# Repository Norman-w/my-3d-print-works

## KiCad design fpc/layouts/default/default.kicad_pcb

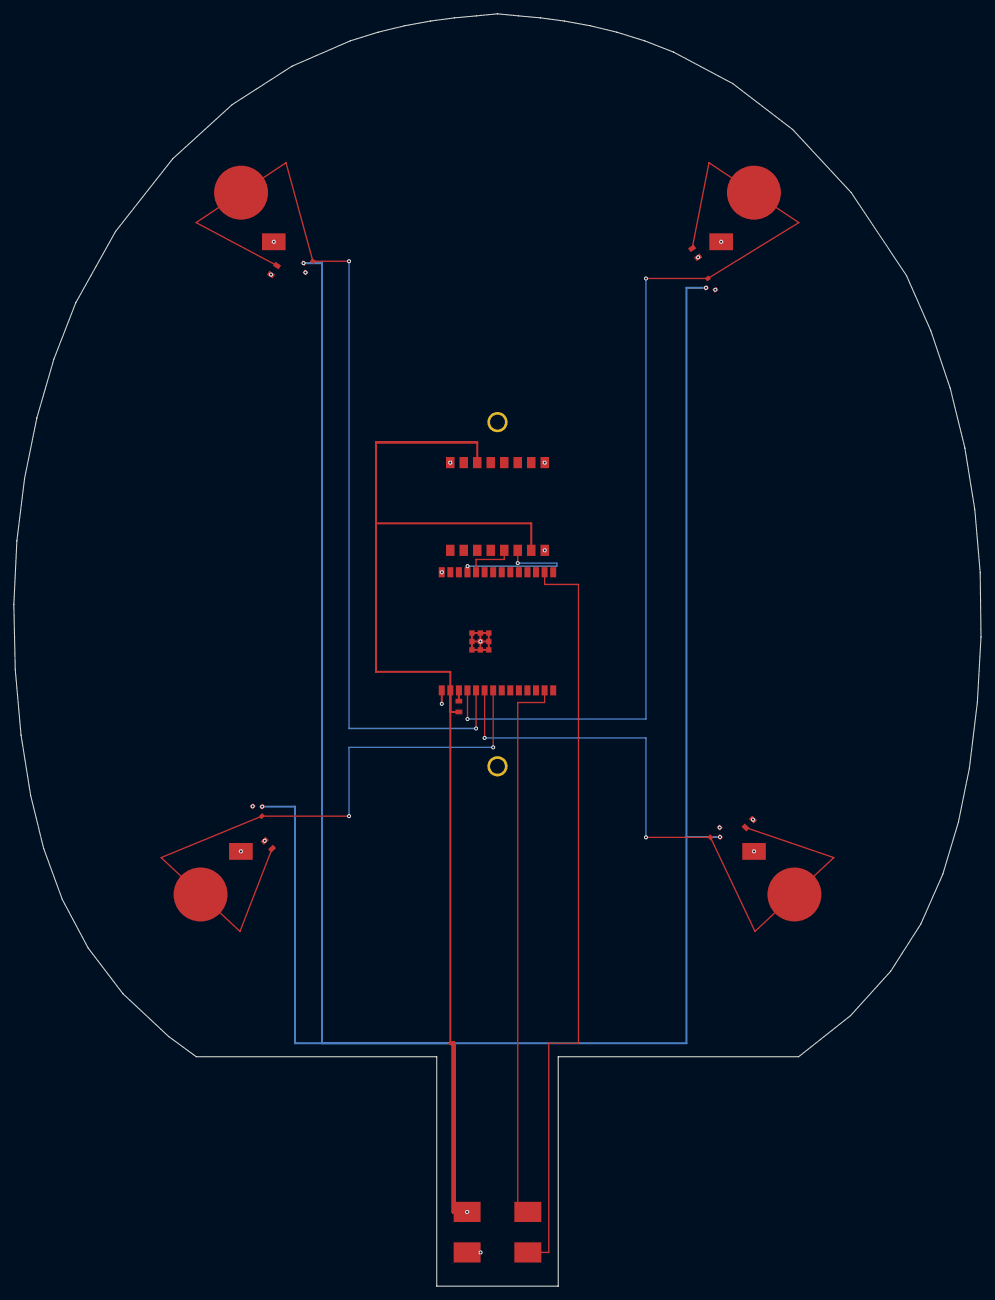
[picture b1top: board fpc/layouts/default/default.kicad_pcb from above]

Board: 2 copper layers, 143.3 x 188.5 mm, 19 parts (0 on the bottom side), 11 nets.

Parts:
D_PZT_BL: BAT54S
D_PZT_BR: BAT54S
D_PZT_TL: BAT54S
D_PZT_TR: BAT54S
J1: ESP32-C6-WROOM-1
PZT_BL: PZT-5A
PZT_BR: PZT-5A
PZT_TL: PZT-5A
PZT_TR: PZT-5A
R_EN: 10k
R_PZT_BL: 1M
R_PZT_BR: 1M
R_PZT_TL: 1M
R_PZT_TR: 1M
TP_D+: D+
TP_D-: D-
TP_GND: GND
TP_VCC: VCC
U1: IM948

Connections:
EN: J1.3, R_EN.1
GND: D_PZT_BL.2, D_PZT_BR.2, D_PZT_TL.2, D_PZT_TR.2, J1.1, J1.28, J1.29, PZT_BL.2, PZT_BR.2, PZT_TL.2, PZT_TR.2, R_PZT_BL.2, R_PZT_BR.2, R_PZT_TL.2, R_PZT_TR.2, TP_GND.1, U1.1, U1.8, U1.16
PZT_BL_SIGNAL: D_PZT_BL.1, J1.7, PZT_BL.1, R_PZT_BL.1
PZT_BR_SIGNAL: D_PZT_BR.1, J1.6, PZT_BR.1, R_PZT_BR.1
PZT_TL_SIGNAL: D_PZT_TL.1, J1.5, PZT_TL.1, R_PZT_TL.1
PZT_TR_SIGNAL: D_PZT_TR.1, J1.4, PZT_TR.1, R_PZT_TR.1
UART_RX: J1.25, U1.14
UART_TX: J1.24, U1.13
USB_D+: J1.13, TP_D+.1
USB_D-: J1.16, TP_D-.1
VCC: D_PZT_BL.3, D_PZT_BR.3, D_PZT_TL.3, D_PZT_TR.3, J1.2, R_EN.2, TP_VCC.1, U1.3, U1.15

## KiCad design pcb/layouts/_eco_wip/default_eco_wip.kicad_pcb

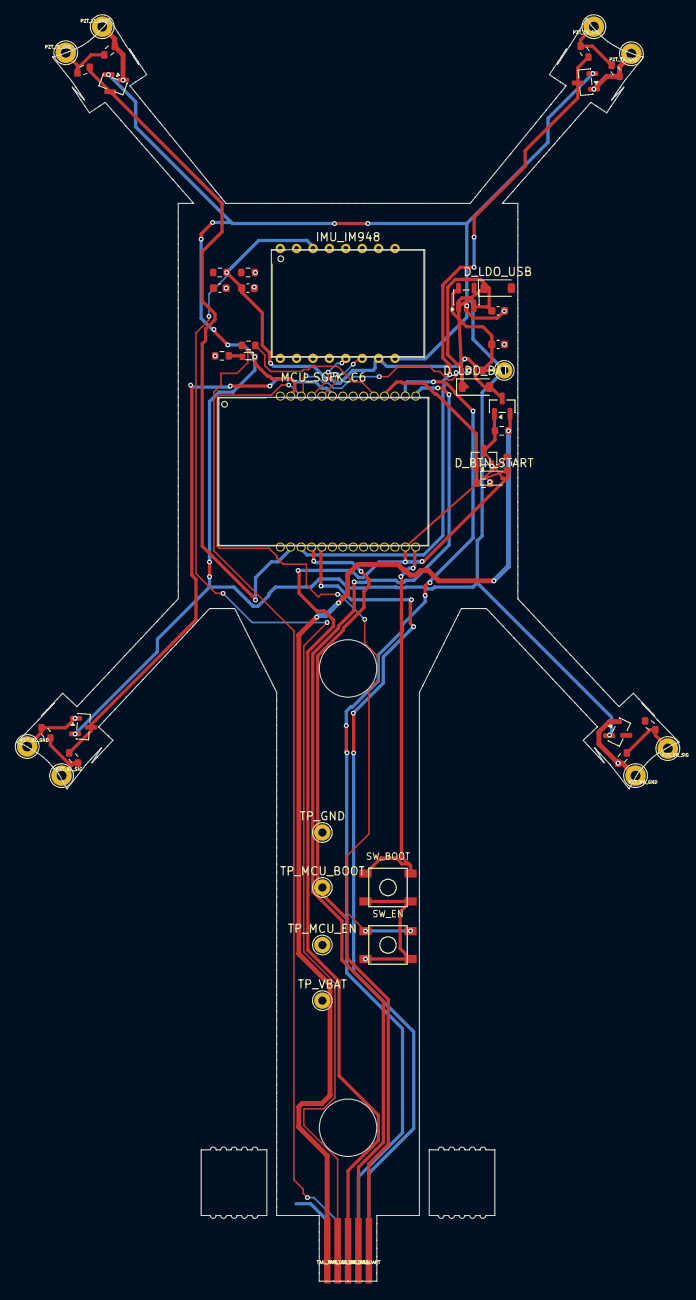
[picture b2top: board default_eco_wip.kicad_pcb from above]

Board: 2 copper layers, 80.8 x 153.9 mm, 53 parts (0 on the bottom side), 30 nets.

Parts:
BAT_C_ADC_100N: C_0603_1608Metric
BAT_R_BOT_1M: R_0603_1608Metric
BAT_R_TOP_1M: R_0603_1608Metric
D_BTN_START: 1N4148W; D_SOD-323
D_LDO_BAT: SS14; D_SOD-123
D_LDO_USB: SS14; D_SOD-123
IMU_IM948: IM948_CUTOUT
LED_C_SUP_100N: C_0603_1608Metric
LED_MCU_PWR: LED_0603
LED_R_DATA_330R: R_0603_1608Metric
MCU_SGFK_C6: SGFK_ESP32-C6-N8_CUTOUT
PW_C_IN_10U: C_0603_1608Metric
PW_C_OUT_10U: C_0603_1608Metric
PW_LDO_3V3: SOT-23-5
PW_Q_LATCH: SOT-23
PW_Q_LOAD: SOT-23
PW_R_BTN_SER_1K: 1k; R_0603_1608Metric
PW_R_EN_PU_10K: R_0603_1608Metric
PW_R_GATE_100K: R_0603_1608Metric
PW_R_LATCH_PD_100K: R_0603_1608Metric
PZT_BL_D_CLAMP: SOT-23
PZT_BL_GND: TestPoint_THTPad_D2.5mm_Drill1.2mm
PZT_BL_R_DIS_1M: R_0603_1608Metric
PZT_BL_R_SER_4K7: R_0603_1608Metric
PZT_BL_SIG: TestPoint_THTPad_D2.5mm_Drill1.2mm
PZT_BR_D_CLAMP: SOT-23
PZT_BR_GND: TestPoint_THTPad_D2.5mm_Drill1.2mm
PZT_BR_R_DIS_1M: R_0603_1608Metric
PZT_BR_R_SER_4K7: R_0603_1608Metric
PZT_BR_SIG: TestPoint_THTPad_D2.5mm_Drill1.2mm
PZT_TL_D_CLAMP: SOT-23
PZT_TL_GND: TestPoint_THTPad_D2.5mm_Drill1.2mm
PZT_TL_R_DIS_1M: R_0603_1608Metric
PZT_TL_R_SER_4K7: R_0603_1608Metric
PZT_TL_SIG: TestPoint_THTPad_D2.5mm_Drill1.2mm
PZT_TR_D_CLAMP: SOT-23
PZT_TR_GND: TestPoint_THTPad_D2.5mm_Drill1.2mm
PZT_TR_R_DIS_1M: R_0603_1608Metric
PZT_TR_R_SER_4K7: R_0603_1608Metric
PZT_TR_SIG: TestPoint_THTPad_D2.5mm_Drill1.2mm
R_MCU_PWR_1K: R_0603_1608Metric
SW_BOOT: 4.5x4.5; SW_SPST_4.5x4.5
SW_EN: 4.5x4.5; SW_SPST_4.5x4.5
TAIL_CTL: EdgeFingerPad_P1.27mm_Dual
TAIL_LED: EdgeFingerPad_P1.27mm_Dual
TAIL_PWR: EdgeFingerPad_P1.27mm_Dual
TAIL_UART: EdgeFingerPad_P1.27mm_Dual
TAIL_USB: EdgeFingerPad_P1.27mm_Dual
TP_3V3: 3V3; TestPoint_THTPad_D2.0mm_Drill1.0mm
TP_GND: GND; TestPoint_THTPad_D2.0mm_Drill1.0mm
TP_MCU_BOOT: BOOT; TestPoint_THTPad_D2.0mm_Drill1.0mm
TP_MCU_EN: EN; TestPoint_THTPad_D2.0mm_Drill1.0mm
TP_VBAT: VBAT_SW; TestPoint_THTPad_D2.0mm_Drill1.0mm

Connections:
BOOT: MCU_SGFK_C6.15, SW_BOOT.1, TP_MCU_BOOT.1
EN: MCU_SGFK_C6.3, PW_R_EN_PU_10K.1, SW_EN.1, TP_MCU_EN.1
PWR_LATCH: MCU_SGFK_C6.11, PW_Q_LATCH.1, PW_R_LATCH_PD_100K.1
UART_RX: MCU_SGFK_C6.24, TAIL_UART.B
UART_TX: MCU_SGFK_C6.25, TAIL_UART.F
USB_DN: MCU_SGFK_C6.13, TAIL_USB.B
USB_DP: MCU_SGFK_C6.14, TAIL_USB.F
USB_VBUS: D_LDO_USB.2, IMU_IM948.2, TAIL_CTL.B
VBAT_SW: BAT_R_TOP_1M.1, D_LDO_BAT.2, IMU_IM948.3, IMU_IM948.15, LED_C_SUP_100N.1, PW_Q_LOAD.3, TAIL_LED.F, TP_VBAT.1
bleed_resistor-SIGNAL_PAD-0: PZT_BL_R_DIS_1M.1, PZT_BL_R_SER_4K7.1, PZT_BL_SIG.1
bleed_resistor-SIGNAL_PAD-1: PZT_BR_R_DIS_1M.1, PZT_BR_R_SER_4K7.1, PZT_BR_SIG.1
bleed_resistor-SIGNAL_PAD-2: PZT_TL_R_DIS_1M.1, PZT_TL_R_SER_4K7.1, PZT_TL_SIG.1
bleed_resistor-SIGNAL_PAD-3: PZT_TR_R_DIS_1M.1, PZT_TR_R_SER_4K7.1, PZT_TR_SIG.1
btn_sw: D_BTN_START.1, PW_R_BTN_SER_1K.1, TAIL_CTL.F
c: LED_MCU_PWR.2, R_MCU_PWR_1K.1
gnd: BAT_C_ADC_100N.2, BAT_R_BOT_1M.2, IMU_IM948.1, IMU_IM948.8, IMU_IM948.16, LED_C_SUP_100N.2, MCU_SGFK_C6.1, MCU_SGFK_C6.28, PW_C_IN_10U.2, PW_C_OUT_10U.2, PW_LDO_3V3.2, PW_Q_LATCH.2, PW_R_LATCH_PD_100K.2, PZT_BL_D_CLAMP.1, PZT_BL_GND.1, PZT_BL_R_DIS_1M.2, PZT_BR_D_CLAMP.1, PZT_BR_GND.1, PZT_BR_R_DIS_1M.2, PZT_TL_D_CLAMP.1, PZT_TL_GND.1, PZT_TL_R_DIS_1M.2, PZT_TR_D_CLAMP.1, PZT_TR_GND.1, PZT_TR_R_DIS_1M.2, R_MCU_PWR_1K.2, SW_BOOT.2, SW_EN.2, TAIL_PWR.B, TP_GND.1
imu_uart_rx: IMU_IM948.14, MCU_SGFK_C6.5
imu_uart_tx: IMU_IM948.13, MCU_SGFK_C6.4
ldo_vin: D_LDO_BAT.1, D_LDO_USB.1, PW_C_IN_10U.1, PW_LDO_3V3.1, PW_LDO_3V3.3
led_data: LED_R_DATA_330R.1, MCU_SGFK_C6.10
led_din: LED_R_DATA_330R.2, TAIL_LED.B
p_gate: D_BTN_START.2, PW_Q_LATCH.3, PW_Q_LOAD.1, PW_R_GATE_100K.1
pzt_bl_signal: MCU_SGFK_C6.6, PZT_BL_D_CLAMP.3, PZT_BL_R_SER_4K7.2
pzt_br_signal: MCU_SGFK_C6.7, PZT_BR_D_CLAMP.3, PZT_BR_R_SER_4K7.2
pzt_tl_signal: MCU_SGFK_C6.27, PZT_TL_D_CLAMP.3, PZT_TL_R_SER_4K7.2
pzt_tr_signal: MCU_SGFK_C6.26, PZT_TR_D_CLAMP.3, PZT_TR_R_SER_4K7.2
user_btn: MCU_SGFK_C6.16, PW_R_BTN_SER_1K.2
vbat_in: PW_Q_LOAD.2, PW_R_GATE_100K.2, TAIL_PWR.F
vbat_sense: BAT_C_ADC_100N.1, BAT_R_BOT_1M.1, BAT_R_TOP_1M.2, IMU_IM948.7
vcc: LED_MCU_PWR.1, MCU_SGFK_C6.2, PW_C_OUT_10U.1, PW_LDO_3V3.5, PW_R_EN_PU_10K.2, PZT_BL_D_CLAMP.2, PZT_BR_D_CLAMP.2, PZT_TL_D_CLAMP.2, PZT_TR_D_CLAMP.2, TP_3V3.1

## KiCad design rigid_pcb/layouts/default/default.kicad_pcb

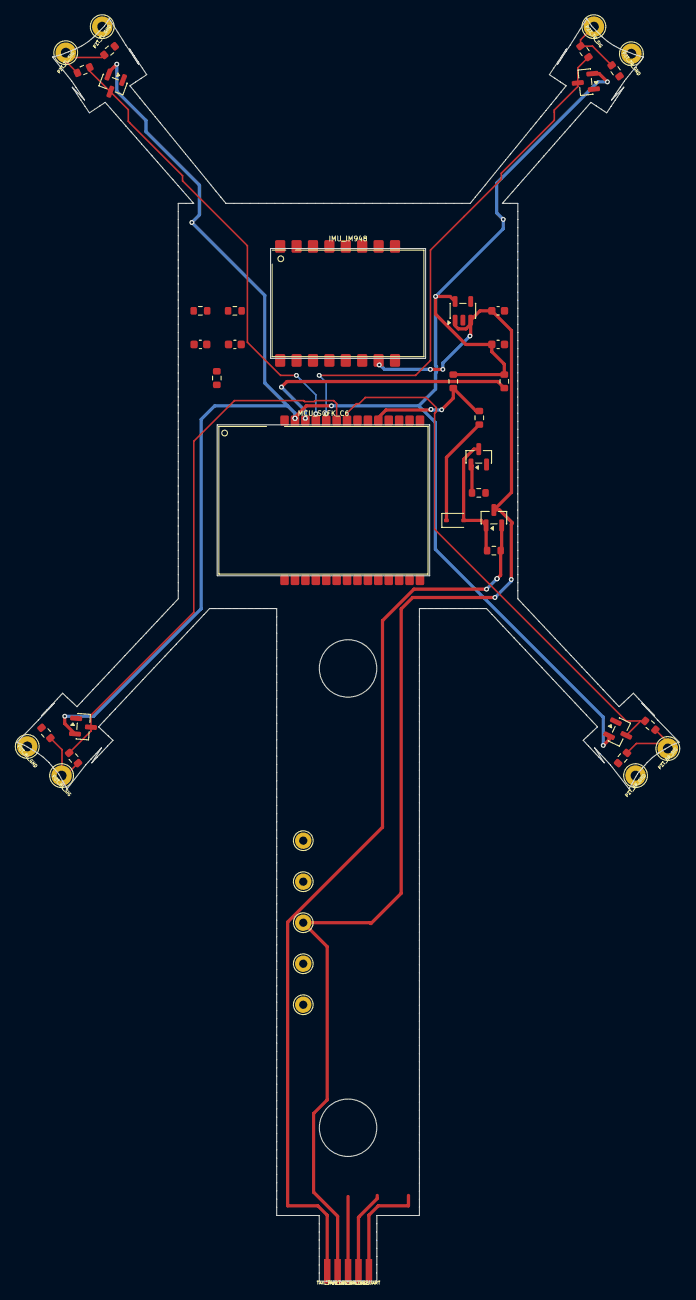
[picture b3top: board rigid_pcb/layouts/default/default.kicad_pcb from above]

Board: 2 copper layers, 80.8 x 153.9 mm, 48 parts (0 on the bottom side), 26 nets.

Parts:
BAT_C_ADC_100N: 100nF; C_0603_1608Metric
BAT_R_BOT_1M: 1M; R_0603_1608Metric
BAT_R_TOP_1M: 1M; R_0603_1608Metric
IMU_IM948: IM948; IM948_CUTOUT
LED_C_SUP_100N: 100nF; C_0603_1608Metric
LED_R_DATA_330R: 330R; R_0603_1608Metric
MCU_SGFK_C6: SGFK ESP32-C6-N8; SGFK_ESP32-C6-N8_CUTOUT
PW_C_IN_10U: 10uF; C_0603_1608Metric
PW_C_OUT_10U: 10uF; C_0603_1608Metric
PW_D_BTN: Schottky; D_SOD-323
PW_LDO_3V3: AP2112K-3.3; SOT-23-5
PW_Q_LATCH: N-MOS latch; SOT-23
PW_Q_LOAD: P-MOS load switch; SOT-23
PW_R_BTN_PU_10K: 10k; R_0603_1608Metric
PW_R_BTN_SER_1K: 1k; R_0603_1608Metric
PW_R_EN_PU_10K: 10k; R_0603_1608Metric
PW_R_GATE_100K: 100k; R_0603_1608Metric
PW_R_LATCH_PD_100K: 100k; R_0603_1608Metric
PZT_BL_D_CLAMP: BAT54S; SOT-23
PZT_BL_GND: PZT GND wire; TestPoint_THTPad_D2.5mm_Drill1.2mm
PZT_BL_R_DIS_1M: 1M; R_0603_1608Metric
PZT_BL_R_SER_4K7: 4.7k; R_0603_1608Metric
PZT_BL_SIG: PZT signal wire; TestPoint_THTPad_D2.5mm_Drill1.2mm
PZT_BR_D_CLAMP: BAT54S; SOT-23
PZT_BR_GND: PZT GND wire; TestPoint_THTPad_D2.5mm_Drill1.2mm
PZT_BR_R_DIS_1M: 1M; R_0603_1608Metric
PZT_BR_R_SER_4K7: 4.7k; R_0603_1608Metric
PZT_BR_SIG: PZT signal wire; TestPoint_THTPad_D2.5mm_Drill1.2mm
PZT_TL_D_CLAMP: BAT54S; SOT-23
PZT_TL_GND: PZT GND wire; TestPoint_THTPad_D2.5mm_Drill1.2mm
PZT_TL_R_DIS_1M: 1M; R_0603_1608Metric
PZT_TL_R_SER_4K7: 4.7k; R_0603_1608Metric
PZT_TL_SIG: PZT signal wire; TestPoint_THTPad_D2.5mm_Drill1.2mm
PZT_TR_D_CLAMP: BAT54S; SOT-23
PZT_TR_GND: PZT GND wire; TestPoint_THTPad_D2.5mm_Drill1.2mm
PZT_TR_R_DIS_1M: 1M; R_0603_1608Metric
PZT_TR_R_SER_4K7: 4.7k; R_0603_1608Metric
PZT_TR_SIG: PZT signal wire; TestPoint_THTPad_D2.5mm_Drill1.2mm
TAIL_CTL: F:BTN B:VBUS; EdgeFingerPad_P1.27mm_Dual
TAIL_LED: F:LED+ B:DIN; EdgeFingerPad_P1.27mm_Dual
TAIL_PWR: F:VBAT B:GND; EdgeFingerPad_P1.27mm_Dual
TAIL_UART: F:TX B:RX; EdgeFingerPad_P1.27mm_Dual
TAIL_USB: F:D+ B:D-; EdgeFingerPad_P1.27mm_Dual
TP_3V3: 3V3 test; TestPoint_THTPad_D2.0mm_Drill1.0mm
TP_BOOT: BOOT test; TestPoint_THTPad_D2.0mm_Drill1.0mm
TP_EN: EN test; TestPoint_THTPad_D2.0mm_Drill1.0mm
TP_GND: GND test; TestPoint_THTPad_D2.0mm_Drill1.0mm
TP_VBAT_SW: VBAT_SW test; TestPoint_THTPad_D2.0mm_Drill1.0mm

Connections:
boot_btn: MCU_SGFK_C6.9, TP_BOOT.1
btn_sw: PW_D_BTN.1, PW_R_BTN_SER_1K.1, TAIL_CTL.F
en: MCU_SGFK_C6.3, PW_R_EN_PU_10K.1, TP_EN.1
gnd: BAT_C_ADC_100N.2, BAT_R_BOT_1M.2, IMU_IM948.1, IMU_IM948.8, IMU_IM948.16, LED_C_SUP_100N.2, MCU_SGFK_C6.1, MCU_SGFK_C6.28, PW_C_IN_10U.2, PW_C_OUT_10U.2, PW_LDO_3V3.2, PW_Q_LATCH.2, PW_R_LATCH_PD_100K.2, PZT_BL_D_CLAMP.1, PZT_BL_GND.1, PZT_BL_R_DIS_1M.2, PZT_BR_D_CLAMP.1, PZT_BR_GND.1, PZT_BR_R_DIS_1M.2, PZT_TL_D_CLAMP.1, PZT_TL_GND.1, PZT_TL_R_DIS_1M.2, PZT_TR_D_CLAMP.1, PZT_TR_GND.1, PZT_TR_R_DIS_1M.2, TAIL_PWR.B, TP_GND.1
led_data: LED_R_DATA_330R.1, MCU_SGFK_C6.8
led_din: LED_R_DATA_330R.2, TAIL_LED.B
p_gate: PW_D_BTN.2, PW_Q_LATCH.3, PW_Q_LOAD.1, PW_R_GATE_100K.1
pwr_latch: MCU_SGFK_C6.11, PW_Q_LATCH.1, PW_R_LATCH_PD_100K.1
pzt_bl-pzt_raw: PZT_BL_R_DIS_1M.1, PZT_BL_R_SER_4K7.1, PZT_BL_SIG.1
pzt_bl_signal: MCU_SGFK_C6.6, PZT_BL_D_CLAMP.3, PZT_BL_R_SER_4K7.2
pzt_br-pzt_raw: PZT_BR_R_DIS_1M.1, PZT_BR_R_SER_4K7.1, PZT_BR_SIG.1
pzt_br_signal: MCU_SGFK_C6.7, PZT_BR_D_CLAMP.3, PZT_BR_R_SER_4K7.2
pzt_tl-pzt_raw: PZT_TL_R_DIS_1M.1, PZT_TL_R_SER_4K7.1, PZT_TL_SIG.1
pzt_tl_signal: MCU_SGFK_C6.4, PZT_TL_D_CLAMP.3, PZT_TL_R_SER_4K7.2
pzt_tr-pzt_raw: PZT_TR_R_DIS_1M.1, PZT_TR_R_SER_4K7.1, PZT_TR_SIG.1
pzt_tr_signal: MCU_SGFK_C6.5, PZT_TR_D_CLAMP.3, PZT_TR_R_SER_4K7.2
uart_rx: IMU_IM948.14, MCU_SGFK_C6.25, TAIL_UART.B
uart_tx: IMU_IM948.13, MCU_SGFK_C6.24, TAIL_UART.F
usb_dn: MCU_SGFK_C6.16, TAIL_USB.B
usb_dp: MCU_SGFK_C6.13, TAIL_USB.F
user_btn: MCU_SGFK_C6.10, PW_R_BTN_PU_10K.1, PW_R_BTN_SER_1K.2
vbat_in: PW_Q_LOAD.2, PW_R_GATE_100K.2, TAIL_PWR.F
vbat_sense: BAT_C_ADC_100N.1, BAT_R_BOT_1M.1, BAT_R_TOP_1M.2, IMU_IM948.7
vbat_sw: BAT_R_TOP_1M.1, IMU_IM948.3, IMU_IM948.15, LED_C_SUP_100N.1, PW_C_IN_10U.1, PW_LDO_3V3.1, PW_LDO_3V3.3, PW_Q_LOAD.3, TAIL_LED.F, TP_VBAT_SW.1
vbus: IMU_IM948.2, TAIL_CTL.B
vcc: MCU_SGFK_C6.2, PW_C_OUT_10U.1, PW_LDO_3V3.5, PW_R_BTN_PU_10K.2, PW_R_EN_PU_10K.2, PZT_BL_D_CLAMP.2, PZT_BR_D_CLAMP.2, PZT_TL_D_CLAMP.2, PZT_TR_D_CLAMP.2, TP_3V3.1
